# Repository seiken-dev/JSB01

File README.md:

# Johann Sebastian Bachってなに？

名前が決まりませんから、私が所有するCDでおそらく最も多い作曲家の名前をつけてみました。

## なにものか？

いろんな方法を使って眼の前のものをスキャンして、その状態を振動で伝えてあげようという手持ちのデバイスです。

## ビルド

PlatformIOを使ってビルドすることを想定しています。Firmwareディレクトリでビルドを行ってください。

## 各ブランチはなんのため？

* Release: リリース用ブランチ。これが製品のファームになります。
* c.mos: c.mosさん作成のコード。実装されたハードウェアの機能が一番先に試せるはず
* ATtiny: ATtiny1614とかをマイコンとして使うブランチ
* ESP32C3: XIAO ESP32C3をマイコンとして使って、esp-idfを開発環境にするブランチ
* RP2040: RP2040あるいは XIAO RP2040を使って、pico-sdkを開発環境にするブランチ
* main: そのうちメインになるだろうブランチ
* Experimental: 各種実験ブランチ。c.mosブランチの次に動く可能性があるブランチ

## 諸々

まだなにもありません。

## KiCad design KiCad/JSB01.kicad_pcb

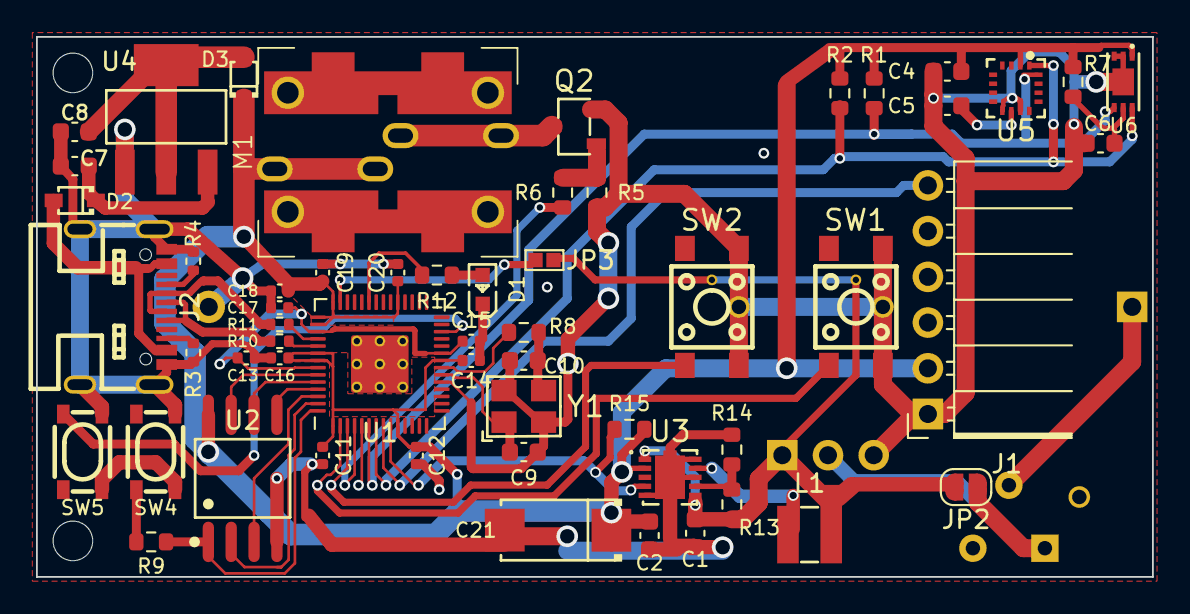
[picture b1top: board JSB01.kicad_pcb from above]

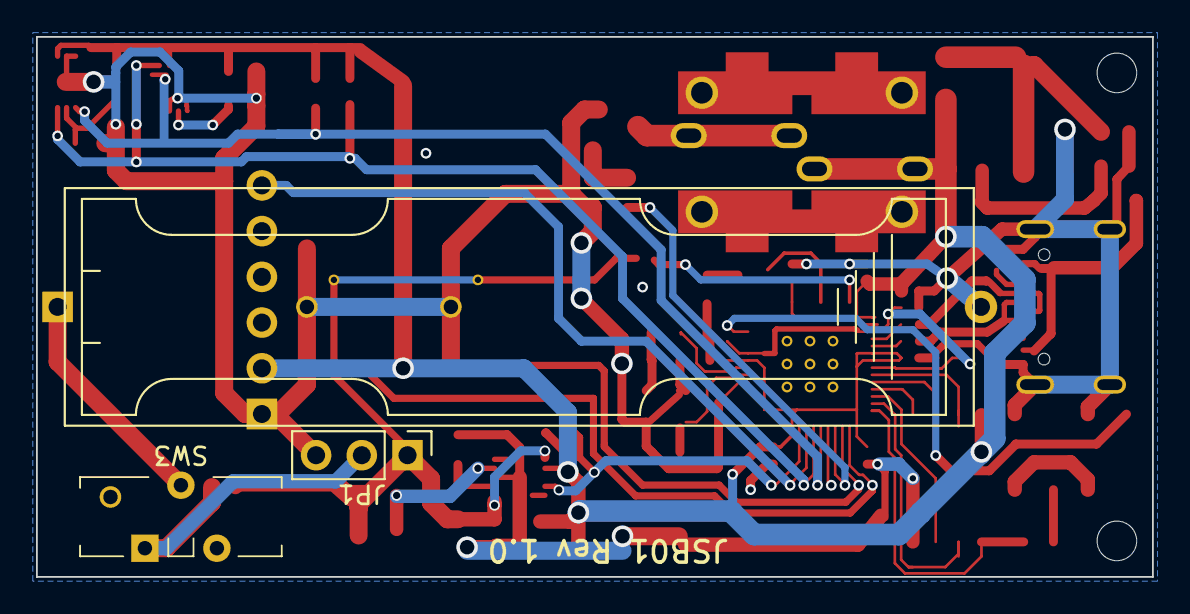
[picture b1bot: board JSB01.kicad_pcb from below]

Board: 2 copper layers, 62.0 x 30.0 mm, 63 parts (3 on the bottom side), 42 nets.

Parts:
BT1: 1xAAA; BatteryHolder_SN4_1PC
C1, C7, C8: 10u; C_0603_1608Metric
C2: 2.2u; C_0603_1608Metric
C4: 0.1u; C_0603_1608Metric
C5: 4.7u; C_0603_1608Metric
C6: 1u; C_0603_1608Metric
C9, C10: 33p; C_0603_1608Metric
C11, C12, C13, C14, C15, C16, C17, C18, C19, C20: 100n; C_0402_1005Metric
C21: 100u; CAP-SMD_L6.0-W3.2
D1: LED; LED0603-RD_GREEN
D2: NSR0320MW2T1G; SOD-323_L1.8-W1.3-LS2.5-RD
D3: 1N5819WS; SOD-323_L1.8-W1.3-LS2.5-RD
J1: MB10XX Sonar; PinSocket_1x06_P2.54mm_Horizontal
J2: USB_C_Receptacle_USB2.0; USB-C-SMD_TYPE-C-16P-1
JP1: for measure I/V; Jumper_1x03_P2.54mm
JP2: SolderJumper_2_Open; SolderJumper-2_P1.3mm_Open_RoundedPad1.0x1.5mm
JP3: SolderJumper_2_Open; SolderJumper-2_Open_mini
L1: 6.8μH; IND-SMD_L3.0-W3.0_VLS3010ET
M1: LD14
Pad: Pad1.2_0.8
Pad#2, Pad#3: Pad0.6_0.35
Pad#4: Pad1.2_0.8
Q2: AO3400A
R1, R2: 4.7K; R_0603_1608Metric
R3, R4: 5.1K; R_0402_1005Metric
R5: 100K; R_0603_1608Metric
R6: 20K; R_0603_1608Metric
R7, R8: 1K; R_0603_1608Metric
R9: 1k; R_0603_1608Metric
R10, R11: 27.4; R_0402_1005Metric
R12: 470; R_0603_1608Metric
R13: 470K; R_0603_1608Metric
R14: 390K; R_0603_1608Metric
R15: 1M; R_0603_1608Metric
SW1, SW2: Tactile; SW-SMD_4P-L4.5-W4.5-P3.00-LS6.8
SW3: Slide; SW_Slide_ESD1752
SW4, SW5: SKRPABE010; KEY-SMD_4P-L4.2-W3.2
U1: RP2040; RP2040-QFN-56
U2: W25Q128JVSIQ; SOP-8-208mil
U3: TPS61025DRCR; VSON-10_L3.0-W3.0-P0.50-BL-EP
U4: AMS1117-3.3; SOT-223-3_L6.5-W3.4
U5: QMC5883P(0x2C); LGA-16_L3.0-W3.0-P0.50-BL_SQ
U6: BH1750FVI(0x23); WSOF-6_L2.6-W1.6-P0.50-TL-EP
Y1: TAXM12M4RLBDDT2T; OSC-SMD_4P-L3.2-W2.5

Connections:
+1V1: C13.1, C15.1, C17.1, U1.23 (DVDD), U1.45 (VREG_VOUT), U1.50 (DVDD)
+3V3: C2.1, C4.1, C11.1, C12.1, C14.1, C16.1, C18.1, C19.1, C20.1, C21.1, D3.1 (K), J1.2 (V+), M1.1 (+), R1.1, R2.1, R7.1, R15.2, U1.1 (IOVDD), U1.10 (IOVDD), U1.22 (IOVDD), U1.33 (IOVDD), U1.42 (IOVDD), U1.43 (ADC_AVDD), U1.44 (VREG_IN), U1.48 (USB_VDD), U1.49 (IOVDD), U2.8 (VCC), U3.2 (VOUT), U5.2 (VDD), U6.1 (VCC)
GND: BT1.2 (-), C1.2, C2.2, C4.2, C5.2, C6.2, C7.2, C8.2, C9.1, C10.1, C11.2, C12.2, C13.2, C14.2, C15.2, C16.2, C17.2, C18.2, C19.2, C20.2, C21.2, D1.1 (K), J1.1 (GND), J2.A1B12 (GND), J2.B1A12 (GND), J2.EP, JP1.3 (B), Q2.2 (S), R3.2, R4.2, R5.2, R14.2, SW1.3, SW1.4, SW2.3, SW2.4, SW4.1, SW5.1, U1.19 (TESTEN), U1.57 (GND), U2.4 (GND), U3.5 (GND), U3.8 (PS), U3.10 (PGND), U3.11 (EP), U4.1 (GND), U5.9 (GND), U5.11 (GND), U6.2 (ADDR), U6.3 (GND), U6.7 (EP), Y1.2 (GND), Y1.4 (GND)
LBO: R15.1, U1.9 (GPIO7), U3.4 (LBO)
unnamed: BT1.1 (+), SW3.2 (B)
unnamed: D1.2 (A), R12.1
unnamed: D2.2 (A), J2.A4B9 (VBUS), J2.B4A9 (VBUS)
unnamed: C7.1, D2.1 (K), U4.3 (VIN)
unnamed: C8.1, D3.2 (A), U4.2 (VOUT), U4.4 (VOUT)
unnamed: J2.A5 (CC1), R4.1
unnamed: J2.B5 (CC2), R3.1
unnamed: C1.1, JP1.1 (A), JP2.2 (B), JP3.1 (A), L1.1, R13.1, U3.1 (EN), U3.6 (VBAT)
unnamed: JP1.2 (C), JP2.1 (A), SW3.1 (A)
unnamed: M1.2 (-), Q2.3 (D)
unnamed: Q2.1 (G), R5.1, R6.2
unnamed: R9.1, SW4.2
unnamed: R12.2, U1.37 (GPIO25)
unnamed: R11.2, U1.46 (USB_DM)
unnamed: R10.2, U1.47 (USB_DP)
unnamed: R13.2, R14.1, U3.7 (LBI)
unnamed: L1.2, U3.9 (SW)
unnamed: C5.1, U5.10 (C1)
unnamed: C6.1, R7.2, U6.5 (DVI)
unnamed: C10.2, R8.1, Y1.3 (OSC2)
QSPI_SCLK: U1.52 (QSPI_SCLK), U2.6 (CLK)
QSPI_SD0: U1.53 (QSPI_SD0), U2.5 (IO0)
QSPI_SD1: U1.55 (QSPI_SD1), U2.2 (IO1)
QSPI_SD2: U1.54 (QSPI_SD2), U2.3 (IO2)
QSPI_SD3: U1.51 (QSPI_SD3), U2.7 (IO3)
QSPI_SS: R9.2, U1.56 (QSPI_SS), U2.1 (~CS)
RESET: SW5.2, U1.26 (RUN)
SCL: R2.2, U1.7 (GPIO5), U5.1 (SCL), U6.6 (SCL)
SDA: R1.2, U1.6 (GPIO4), U5.16 (SDA), U6.4 (SDA)
SONAR_PW: J1.6 (PW), U1.8 (GPIO6)
SW1: SW1.1, SW1.2, U1.2 (GPIO0)
SW2: SW2.1, SW2.2, U1.3 (GPIO1)
USB_DM: J2.A7 (D-), J2.B7 (D-), R11.1
USB_DP: J2.A6 (D+), J2.B6 (D+), R10.1
VBAT: JP3.2 (B), U1.41 (GPIO29_ADC3)
VIB: R6.1, U1.4 (GPIO2)
XIN: C9.2, U1.20 (XIN), Y1.1 (OSC1)
XOUT: R8.2, U1.21 (XOUT)

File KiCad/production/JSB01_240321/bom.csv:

Designator,Footprint,Quantity,Value,LCSC Part #
,,1,,
BT1,BatteryHolder_SN4_1PC,1,1xAAA,
"C1, C7, C8",0603,3,10u,C19702
"C10, C9",0603,2,33p,C1663
"C11, C12, C13, C14, C15, C16, C17, C18, C19, C20",0402,10,100n,C307331
C2,0603,1,2.2u,C23630
C21,CAP-SMD_L6.0-W3.2,1,100u,C183034
C3,0603,1,0.22u,C21120
C4,0603,1,0.1u,C14663
C5,0603,1,4.7u,C19666
C6,0603,1,1u,C15849
D1,LED0603-RD_GREEN,1,LED,C510026
D2,SOD-323_L1.8-W1.3-LS2.5-RD,1,NSR0320MW2T1G,C48192
D3,SOD-323_L1.8-W1.3-LS2.5-RD,1,1N5819WS,C191023
J1,PinSocket_1x06_P2.54mm_Horizontal,1,MB10XX Sonar,
J2,USB-C-SMD_TYPE-C-16P-1,1,USB_C_Receptacle_USB2.0,C2982555
JP2,SolderJumper-2_P1.3mm_Open_RoundedPad1.0x1.5mm,1,SolderJumper_2_Open,
JP3,SolderJumper-2_Open_mini,1,SolderJumper_2_Open,
L1,IND-SMD_L3.0-W3.0_VLS3010ET,1,6.8μH,C404497
Q2,AO3400A,1,AO3400A,C20917
"R1, R2",0603,2,10K,C25804
"R10, R11",0402,2,27.4,C274349
R12,0603,1,470,C23179
R13,0603,1,470K,C23178
R14,0603,1,390K,C23150
R15,0603,1,1M,C22935
"R3, R4",0402,2,5.1K,C25905
R5,0603,1,100K,C25803
R6,0603,1,20K,C4184
"R7, R8, R9",0603,3,1K,C21190
"SW1, SW2",SW-SMD_4P-L4.5-W4.5-P3.00-LS6.8,2,Tactile,C2888900
"SW4, SW5",KEY-SMD_4P-L4.2-W3.2,2,SKRPABE010,C115360
U1,RP2040-QFN-56,1,RP2040,C2040
U2,SOP-8-208mil,1,W25Q128JVSIQ,C97521 
U3,VSON-10_L3.0-W3.0-P0.50-BL-EP,1,TPS61025DRCR,C71369
U4,SOT-223-3_L6.5-W3.4,1,AMS1117-3.3,C6186
U5,LGA-16_L3.0-W3.0-P0.50-BL_SQ,1,QMC5883L(0x0D),C976032
U6,WSOF-6_L2.6-W1.6-P0.50-TL-EP,1,BH1750FVI(0x23),C78960
Y1,OSC-SMD_4P-L3.2-W2.5,1,TAXM12M4RLBDDT2T,C133334

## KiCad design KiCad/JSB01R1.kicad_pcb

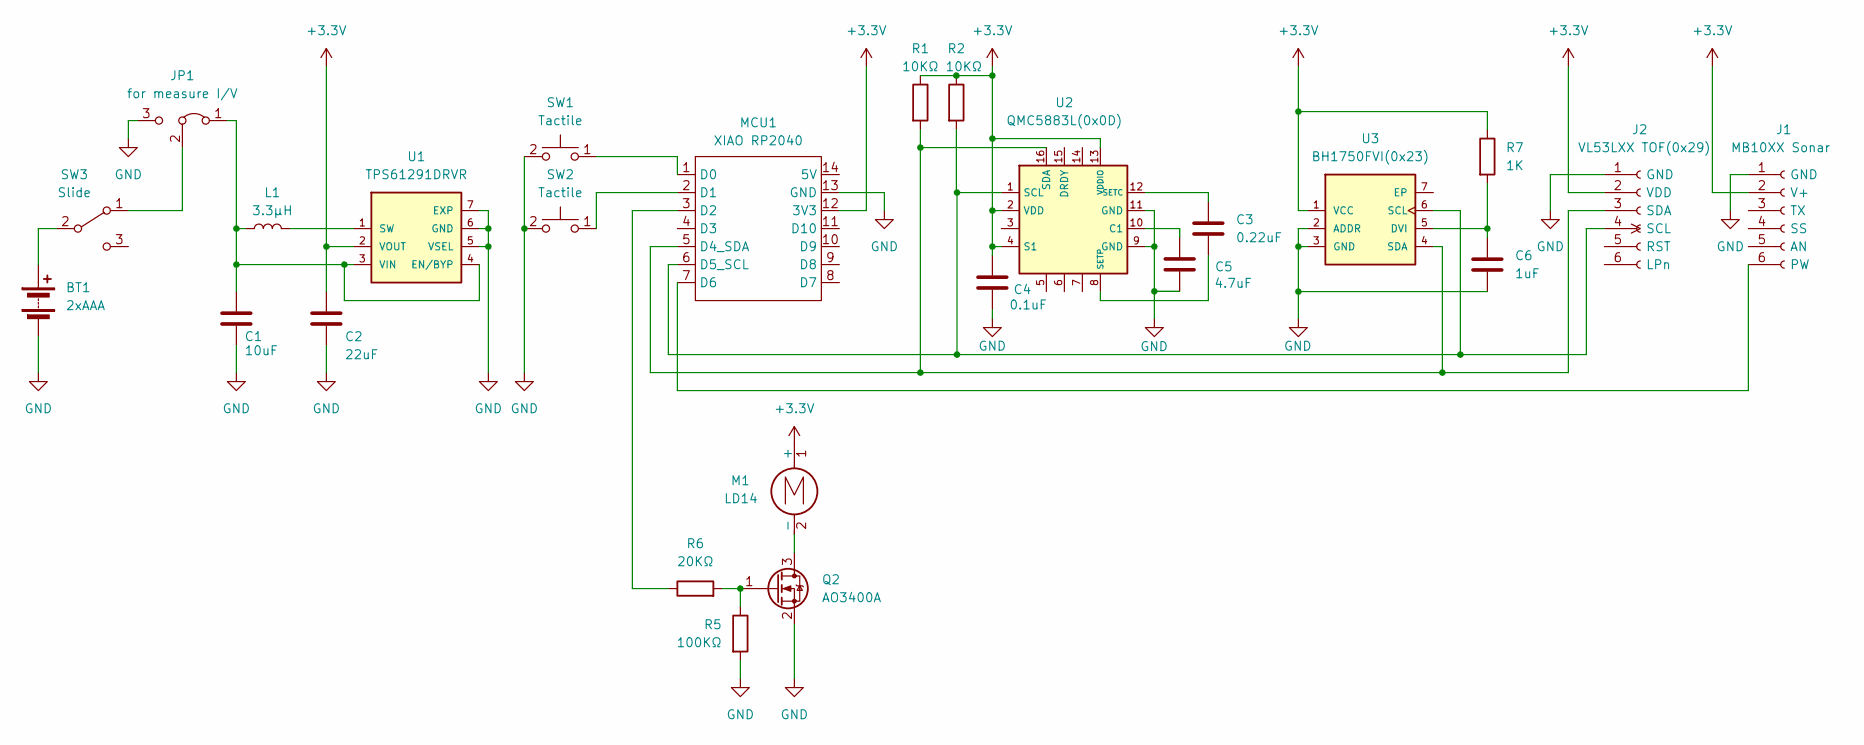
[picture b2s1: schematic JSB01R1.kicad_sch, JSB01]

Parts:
BT1: 2xAAA; BatteryHolder 2xAAA
C1: 10uF; C_0603_1608Metric; LCSC C19702
C2: 22uF; C_0603_1608Metric; LCSC C59461
C3: 0.22uF; C_0603_1608Metric; LCSC C21120
C4: 0.1uF; C_0603_1608Metric; LCSC C14663
C5: 4.7uF; C_0603_1608Metric; LCSC C19666
C6: 1uF; C_0603_1608Metric; LCSC C15849
J1: MB10XX Sonar; PinSocket_1x06_P2.54mm_Horizontal
J2: VL53LXX TOF(0x29); PinSocket_1x06_P2.54mm_Vertical
JP1: for measure I/V; Jumper_1x03_P2.54mm
L1: 3.3μH; IND-SMD_L3.0-W3.0_VLS3010ET; LCSC C136236
M1: LD14
MCU1: XIAO RP2040; MOUDLE14P-2.54-21X17.8MM
Q2: AO3400A; SOT-23; LCSC C20917
R1, R2: 10KΩ; R_0603_1608Metric; LCSC C25804
R5: 100KΩ; R_0603_1608Metric; LCSC C25803
R6: 20KΩ; R_0603_1608Metric; LCSC C4184
R7: 1K; R_0603_1608Metric; LCSC C21190
SW1, SW2: Tactile; SW_tactile_DTS6
SW3: Slide; SW_Slide_ESD1752
U1: TPS61291DRVR; WSON-6_L2.0-W2.0-P0.65-BL-EP; LCSC C464809
U2: QMC5883L(0x0D); LGA-16_L3.0-W3.0-P0.50-BL_SQ; LCSC C976032
U3: BH1750FVI(0x23); WSOF-6_L2.6-W1.6-P0.50-TL-EP; LCSC C78960

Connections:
+3.3V: C2.1, C4.1, J1.2 (V+), J2.2 (VDD), M1.1 (+), MCU1.12 (3V3), R1.1, R2.1, R7.1, U1.2 (VOUT), U2.2 (VDD), U2.4 (S1), U2.13 (VDDIO), U3.1 (VCC)
GND: BT1.2 (-), C1.2, C2.2, C4.2, C5.2, C6.2, J1.1 (GND), J2.1 (GND), JP1.3 (B), MCU1.13 (GND), Q2.2 (S), R5.2, SW1.2, SW2.2, U1.5 (VSEL), U1.6 (GND), U1.7 (EXP), U2.9 (GND), U2.11 (GND), U3.2 (ADDR), U3.3 (GND)
unnamed: BT1.1 (+), SW3.2 (B)
unnamed: J1.6 (PW), MCU1.7 (D6)
unnamed: J2.4 (SCL), MCU1.6 (D5_SCL), R2.2, U2.1 (SCL), U3.6 (SCL)
unnamed: J2.3 (SDA), MCU1.5 (D4_SDA), R1.2, U2.16 (SDA), U3.4 (SDA)
unnamed: C1.1, JP1.1 (A), L1.1, U1.3 (VIN), U1.4 (EN/BYP)
unnamed: JP1.2 (C), SW3.1 (A)
unnamed: M1.2 (-), Q2.3 (D)
unnamed: MCU1.1 (D0), SW1.1
unnamed: MCU1.2 (D1), SW2.1
unnamed: MCU1.3 (D2), R6.1
unnamed: Q2.1 (G), R5.1, R6.2
unnamed: L1.2, U1.1 (SW)
unnamed: C5.1, U2.10 (C1)
unnamed: C3.1, U2.12 (SETC)
unnamed: C3.2, U2.8 (SETP)
unnamed: C6.1, R7.2, U3.5 (DVI)

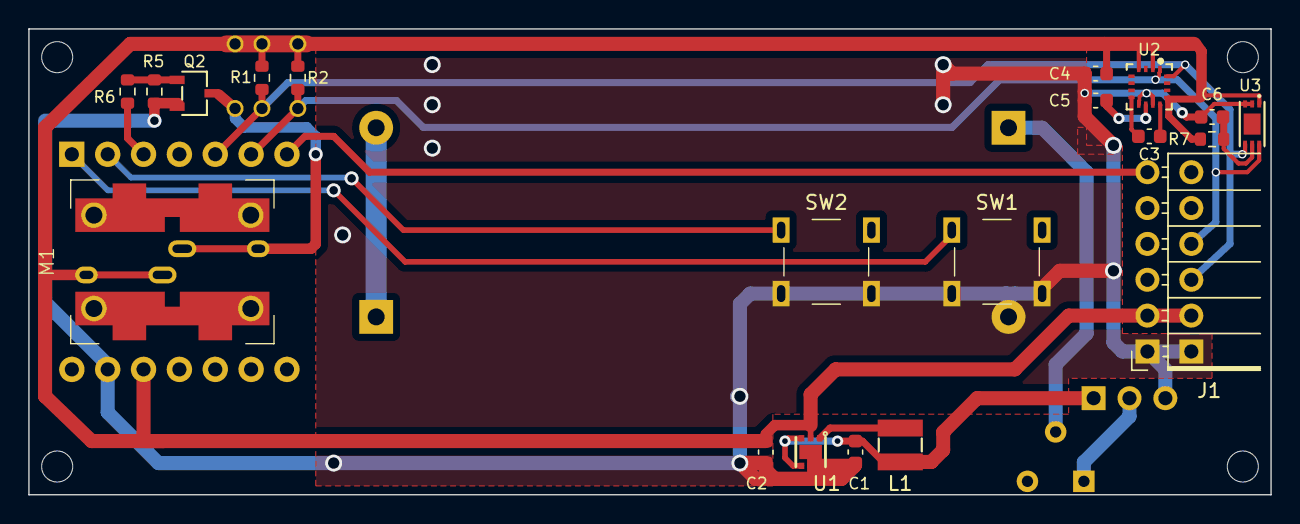
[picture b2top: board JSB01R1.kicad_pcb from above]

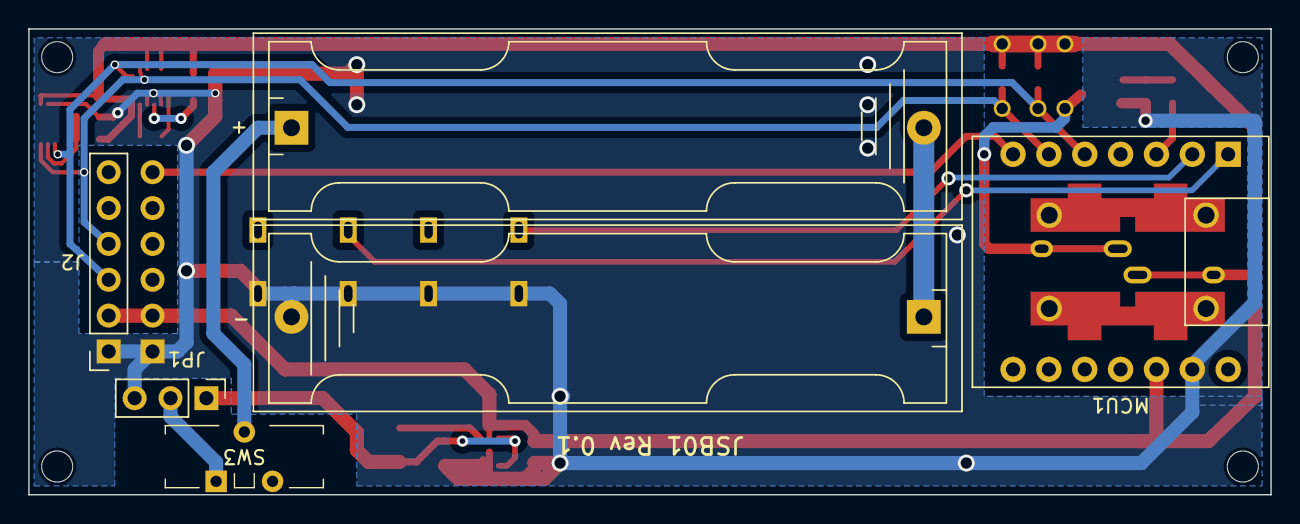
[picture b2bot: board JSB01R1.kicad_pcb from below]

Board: 2 copper layers, 88.0 x 33.0 mm, 31 parts (5 on the bottom side), 18 nets.

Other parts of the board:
Pad: Pad1.2_0.8
Pad#2, Pad#3, Pad#4, Pad#5, Pad#6: Pad1.2_0.8

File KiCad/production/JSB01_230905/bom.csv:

Designator,Footprint,Quantity,Value,LCSC Part #
C1,0603,1,10uF,C19702
C2,0603,1,22uF,C59461
C3,0603,1,0.22uF,C21120
C4,0603,1,0.1uF,C14663
C5,0603,1,4.7uF,C19666
C6,0603,1,1uF,C15849
J1,PinSocket_1x06_P2.54mm_Horizontal,1,MB10XX Sonar,
L1,IND-SMD_L3.0-W3.0_VLS3010ET,1,3.3μH,C136236
M1,LD14,1,LD14,
Q2,AO3400A,1,AO3400A,C20917
"R1, R2",0603,2,10KΩ,C25804
R5,0603,1,100KΩ,C25803
R6,0603,1,20KΩ,C4184
R7,0603,1,1K,C21190
U1,WSON-6_L2.0-W2.0-P0.65-BL-EP,1,TPS61291DRVR,C464809
U2,LGA-16_L3.0-W3.0-P0.50-BL_SQ,1,QMC5883L(0x0D),C976032
U3,WSOF-6_L2.6-W1.6-P0.50-TL-EP,1,BH1750FVI(0x23),C78960

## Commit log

2023-07-19 * First commit. ビルドできないよお。
2023-07-27 とりあえずビルドできる状態。
2023-07-27 * スケルトンみたいなものを作っておこう。
2023-07-28 Fix.
2023-07-28 * testing now!
2023-07-28 * RP2040 version. Created by c.mos
2023-07-28 * use pico_sdk
2023-07-28 * ビルド関係のファイルをgit管理から外した。
2023-07-28 * ひたすら距離を測るだけ。眼の前の障害物に対して、どの程度の反応ができるかをテストするためのコード。
2023-07-28 * readme書きました。
2023-07-29 * MB10XXの反応を確認するためのテスト。 できるだけ計測してからの遅延が発生しないように配慮したつもり。
2023-07-29 * MB10X0, X3を識別できるようにした。適当に補正する。
2023-07-30 * 同じような実験を、VL53L1でもやれるようにした。 * Sparkfunのライブラリを使うようにしてみた。
2023-07-30 * Add readme.
2023-07-30 * Delete unused file.
2023-07-31 * ESP32C3でも同じように動作するように修正。
2023-07-31 * 動作中のログデータを取る準備。
2023-08-01 * 美しくないけど、ログが取れる。 * 下ボタンを数回押して、検出スレッショルドを０にすると、ログの記録が止まる。
2023-08-01 support VL53L5CX
2023-08-02 * Convert CR+LF to LF.
2023-08-03 * 振動フィードバックのサブルーチン軍。
2023-08-03 * VL53L5CXの準備。
2023-08-04 * 各種振動パターンのテスト。
2023-08-04 * とりあえず、MBセンサーっで即時フィードバックができるようにしてみた。切り替え機能はまだない。
2023-08-05 * ヘッダファイルが欠けてたね。
2023-08-11 * とりあえず作った。
2023-08-11 * フィードバックの切替時に、振動が停止しなくなることがある問題を修正。
2023-08-11 * c.mosさん作のTOFセンサーコードをマージ。
2023-08-14 * TOFセンサーのコードを動作するようにした。
2023-08-16 * とりあえずD10にビープを接続できるように、スイッチ類とバイブレーションのピンを初期化するだけ。ゆるゆると行こう。
2023-08-16 * いくつかのファイルをgit管理から外す。
2023-08-16 * ATtinyで動かせるように、最低限の状況で作っている。とりあえず、ビルドが通るだけ。
2023-08-25 * 諸々、変更してみた。ごめん、diff見てね。
2023-09-01 * ビープ関連を修正 * GPIOが読めるかもしれない
2023-09-01 * ピン番号の間違いを修正 * メインループからスイッチ状態を取得してみた
2023-09-02 * しきりなおしだよお！
2023-09-03 * とりあえず超音波センサーの測距
2023-09-04 * 振動モーターの準備
2023-09-05 * タイマーで振動モーターを叩いてみる。
2023-09-05 * RP2040でも、とりあえずPWMが出せるようになったはず。
2023-09-06 * 振動時間を設定して呼び出せる関数を追加。ノンブロッキングの予定。
2023-09-07 * LD14クラスの修正に合わせて変更。
2023-09-07 * 測距してみたよ。
2023-09-07 * クラス名変更 * シリアルの速度をちゃんと指定した。
2023-09-08 * 振動フィードバックのコードを追加。
2023-09-08 * 距離に応じたフィードバックの準備
2023-09-08 * 測距とフィードバックを同時に行ってみる。
2023-09-09 * なんとなくフィードバックパターンを書いてみた。エラーチェックとかちゃんとしてないので、パニックするかも。
2023-09-09 * LD14の初期設定周波数を126Hzに変更 * フィードバックパターンを再定義 * vib.off()の呼び出しは削除
2023-09-09 * RP2040ではtone()を使うように変更
2023-09-10 * 電源投入時にMB10XXが初期化されないのを修正。
2023-09-10 * ESP32C3でも動くようにしたつもり。
2023-09-16 support QMC5883L and BH1750FVI
2023-09-16 fix compass angle
2023-09-16 * 試作機 No.2 * ピンの変更 * 振動デバイスの変更
2023-09-17 * パターンが切り替えられたとき、フィードバック中のパターンをキャンセルするようにしてみた。
2023-09-20 * ボタン操作関連を再度追加。
2023-09-20 support QMC5883L calibration
2023-09-20 * ボタン操作関連
2023-09-29 * 光センサー
2023-10-12 * コンパスのコードをとりあえず入れた。
2023-10-13 * メインループに取り込んでみようかなと思った。
2023-11-16 * 振動のパラメータ微調整。
2023-11-16 * ディレクトリ構成を変更。
2023-11-17 * ディレクトリ構造変更
2023-11-18 support Rev.3 board
2023-11-18 Create LICENSE
2023-11-21 add KiCad,Blender filles
2023-11-21 modify README
2023-11-21 * Raspberry Pi Pico互換ボードとして設定。
2023-11-21 * Fix typo.
2023-11-21 * ハードウェアの作成プロジェクトファイルを追加。
2023-11-23 css test
2023-11-23 add CC license
2023-12-08 * SEEED XIAO NRF52840 support.
2023-12-11 * とりあえず距離測定してフィードバックするまでやった。狙い通りかなり省電力。
2023-12-12 * 測定中に距離を取得してしまうと不正な値が返ってくるのを回避。
2023-12-28 * MB10XXでの測距部分を分離など。
2024-01-09 * ウェブサイト公開準備
2024-01-09 * ウェブサイトのソースディレクトリを変更
2024-01-09 * GitHub pagesの設定を一時的に削除
2024-01-09 * GitHub pagesのテスト中
2024-01-12 * デフォルトターゲットをrpipicoに変更
2024-01-12 * MB10x0からのRisingとFallingの割り込みを取り違えても対処できるようにしてみた。
2024-01-13 * Testing...
2024-01-22 * 近接したときも振動が止まらないように修正。
2024-01-22 * 追加し忘れていたので設定ファイルを追加。
2024-02-27 * 使用中に物体がないのに近距離でフリーズすることがあるようなので、最大検出距離を220インチに変更。
2024-03-11 * CPUクロックを設定。省電力のため。
2024-03-11 * 5Mのバイブレーションパターンが未登録だったようなので修正。
2024-03-11 * フォルダ移動後追加していなかったので、.gitignoreを修正して追加。VSCode, Emacsの作業ファイルを追加。
2024-03-11 * XIAO ESP32C3でコンパイルが通らなくなっていたので修正。
2024-03-11 * 照度センサー機能を追加。上ボタン押しながら電源On
2024-03-12 * 光量が０のときの対策が落ちていたので追加。
2024-03-16 * 1回の振動の長さを5mSecから10mSecにしてみた。
2024-03-29 * 明るさが2048Lxを超えたときに振動感覚が不正な値になるかもしれないのに対処。
2024-03-31 update case model
2024-04-15 * System clock speed changed.
2024-05-29 testing
2025-05-19 * Fix image link.
2025-05-20 replace with R6 photo
2025-06-05 add caseR5,R6
2025-07-03 New pico-sdk version stated.
2025-07-11 * コンパスのためにデバイスの設定情報を保存する機能を追加
2025-08-23 support QMC5883P
2025-09-03 BTO ver. (QMC5883P)
2025-09-03 BH1750FVI move to left
2025-09-04 add caseR10
2025-09-15 change to 'board=pico'
2025-10-02 * プラットフォームを明示的に指定した。
2025-10-15 * Compass implementation.
2025-10-17 * コンパスの初期対応 * Boardクラス名を変更
2025-12-31 New branch
2025-12-31 * maxgerhardtさんのplatformを使う必要があるため、これを標準の環境に混在させないように設定を追加。
2025-12-31 * ソースコードのフォーマットを行った。 * 使わない環境をplatformio.iniから削除した。
2026-01-02 * 関数仕様のコメントを追加。 * ビルドエラーになる可能性があるのでincludeの順番を修正。
2026-01-02 * ソナーモード時、スイッチを同時(10mSec以内)に押した際にリセットされなかったのを修正。
2026-01-06 * c.mosブランチから、ハードウェア設計関連ファイルを追加
2026-01-06 * Add Python virtual environment.
2026-01-06 * ファームウェア書き込み用のプログラムを追加。リリースする際にハッシュを更新してください。
2026-01-06 * Add License
2026-01-06 * 書き込み後のエラー処理を堅牢にした。
2026-01-06 * README.mdの配布ファイルの実行方法を明確化
2026-01-07 * コンパス機能を実装。下ボタンを押しながら起動。コンパス中に上下ボタンの長押しで３０秒のキャリブレーション。 * 不要なPreferencesモジュールを削除。 * main.cppのコードを整理。
2026-01-07 * 1.0RC1用にハッシュを更新 * バイナリの出力先を変更
2026-01-08 * 生成された書き込みツールがウィルスと誤検出される問題を修正 * pico-flasher の依存関係を更新
2026-01-12 * ファームウェア書き込みツールをGo言語で実装
2026-01-12 * Go言語で実装したため、Python版を削除 * PyInstallerで作成した実行ファイルにはセキュリティソフトウェアによる 誤検出のリスクがあるため、GOで再実装
2026-01-13 * ユーザ用のドキュメントを追加
2026-01-13 * Update Taskfile.yml to version 1.0RC3 and adjust build commands
2026-01-15 * 複数のRP2040が接続されていたらエラーになるように変更。 * コマンドライン引数 `-p` でシリアルポートを指定できるように変更。
2026-01-20 * I2Cのクロックを100kHzに設定。ハードウェアのトラブルを避けるため。
2026-02-10 * GUIモードの実装開始
2026-02-14 * スクリーンリーダー対応のため、.NETアプリケーションに移行しました。
2026-02-15 * Fix build task.
2026-02-18 * Adjust dialog layout.
2026-04-02 * 新しいコンパス MMC5983MAをサポート。
2026-04-02 * 1.0RD6
2026-04-13 * オフセット値がハネイされていなかったのを習性 * チップの角度を９０ｄ補正
2026-04-13 * 1.0RC7
2026-06-18 * Release 1.0
